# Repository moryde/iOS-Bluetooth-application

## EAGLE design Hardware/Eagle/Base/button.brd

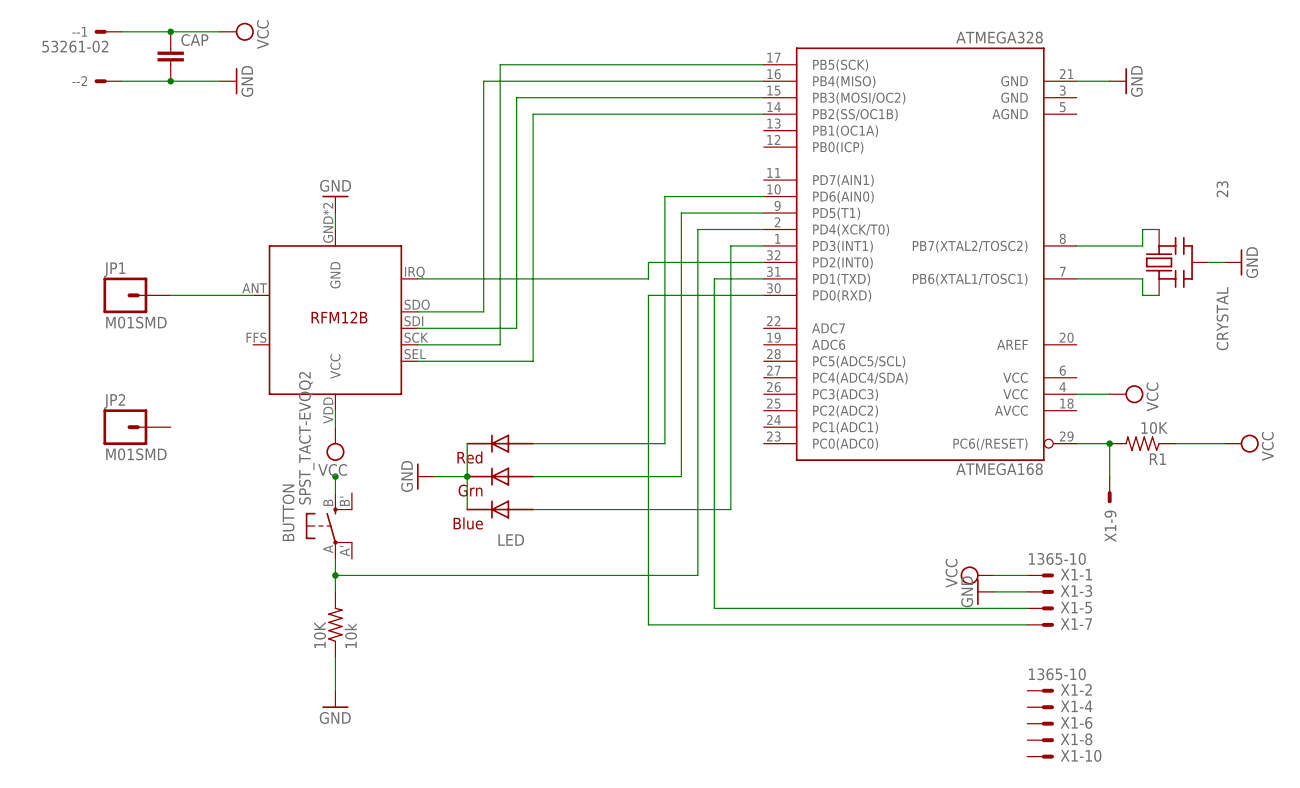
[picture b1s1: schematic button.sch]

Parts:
10K: 10k; R1206
-: 53261-02
ATMEGA328: ATMEGA168; TQFP32-08
BUTTON: SPST_TACT-EVQQ2; EVQ-Q2
CAP: CAP1206; 1206
CRYSTAL: 23; CSTCR-G
JP1, JP2: M01SMD; LUXEON-PAD
LED: RGBLED5050
R1: 10K; R1206
RFM12B: RFM12B
X1: 1365-10

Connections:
5V: -.1, ATMEGA328.4 (VCC), BUTTON.B (S), CAP.1, R1.1, RFM12B.VDD (VCC), X1.1
BUTTON_PIN: 10K.2, ATMEGA328.2 (PD4(XCK/T0)), BUTTON.A
GND: 10K.1, -.2, ATMEGA328.21 (GND), CAP.2, CRYSTAL.2 (GND), LED.4 (BLUE_C), LED.5 (RED_C), LED.6 (GREEN_C), RFM12B.GND, RFM12B.P$12 (GND), X1.3
unnamed: ATMEGA328.8 (PB7(XTAL2/TOSC2)), CRYSTAL.3 (OUT)
unnamed: ATMEGA328.17 (PB5(SCK)), RFM12B.SCK
unnamed: ATMEGA328.15 (PB3(MOSI/OC2)), RFM12B.SDI
unnamed: ATMEGA328.14 (PB2(SS/OC1B)), RFM12B.SEL
unnamed: ATMEGA328.16 (PB4(MISO)), RFM12B.SDO
unnamed: ATMEGA328.7 (PB6(XTAL1/TOSC1)), CRYSTAL.1 (IN)
unnamed: ATMEGA328.1 (PD3(INT1)), LED.3 (BLUE_A)
unnamed: ATMEGA328.32 (PD2(INT0)), RFM12B.IRQ
unnamed: JP1.P$1, RFM12B.ANT
unnamed: ATMEGA328.10 (PD6(AIN0)), LED.2 (RED_A)
unnamed: ATMEGA328.9 (PD5(T1)), LED.1 (GREEN_A)
unnamed: ATMEGA328.31 (PD1(TXD)), X1.5
unnamed: ATMEGA328.30 (PD0(RXD)), X1.7
NANE: ATMEGA328.29 (PC6(/RESET)), R1.2, X1.9

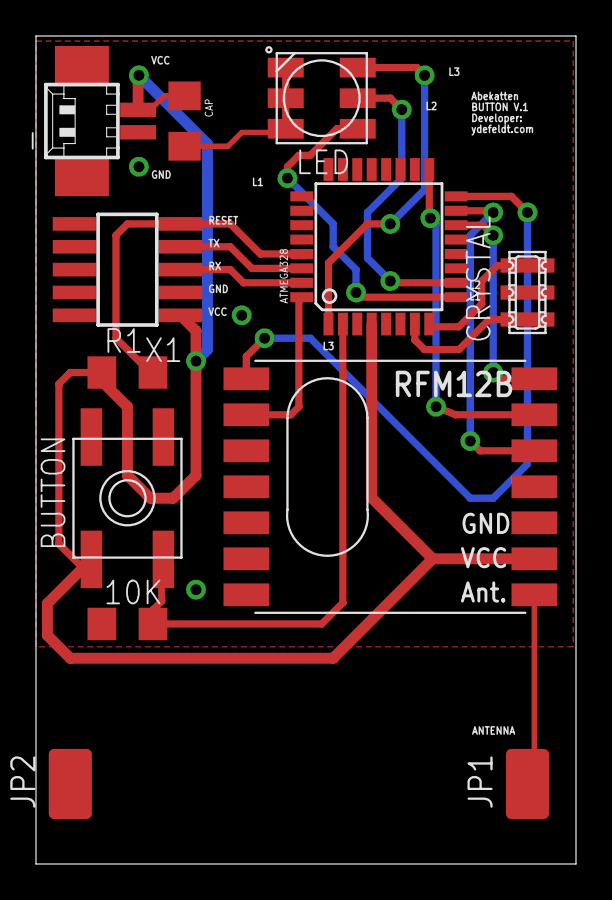
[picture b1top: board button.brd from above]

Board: 2 copper layers, 30.0 x 46.0 mm, 12 parts (0 on the bottom side), 17 nets.

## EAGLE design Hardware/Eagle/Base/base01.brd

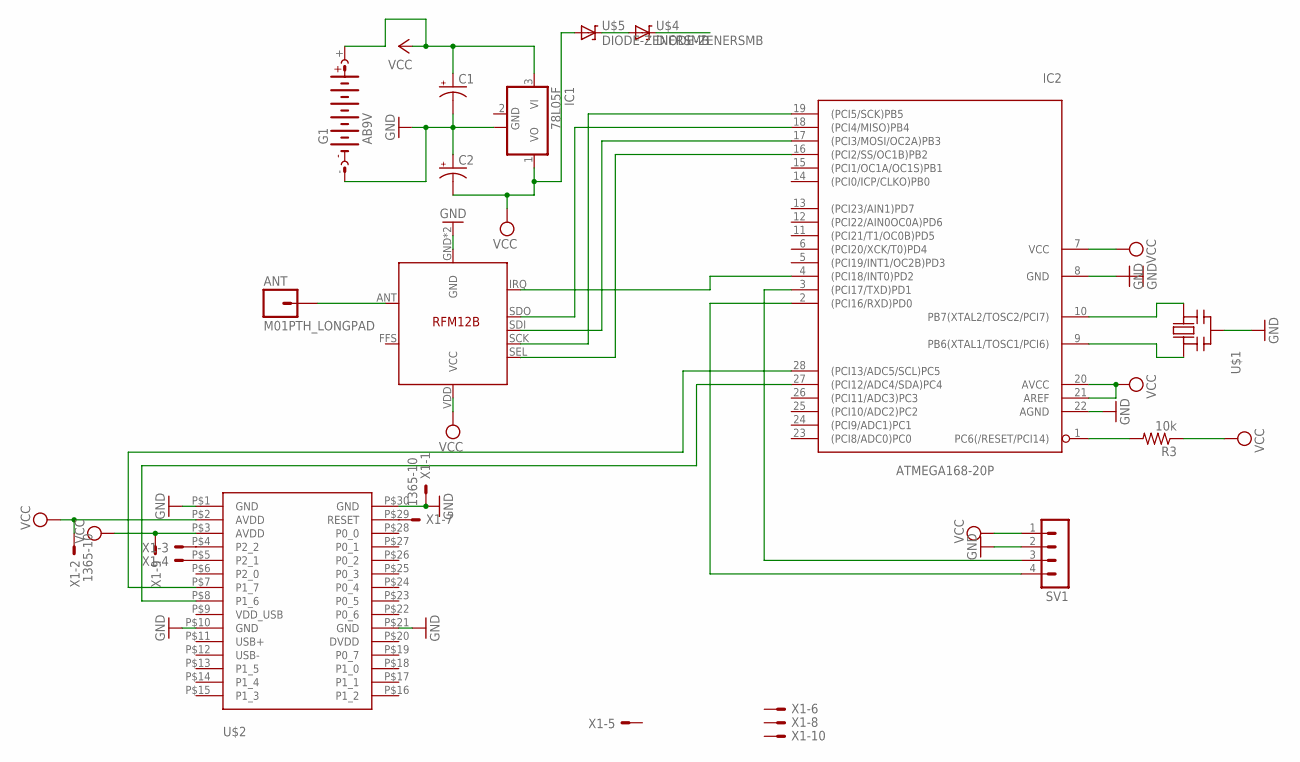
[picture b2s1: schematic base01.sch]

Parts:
ANT: M01PTH_LONGPAD; 1X01_LONGPAD
C1, C2: CAP_POLC; PANASONIC_C
G1: AB9V
IC1: 78L05F; SOT89
IC2: ATMEGA168-20P; DIL28-3
R3: 10k; R2512
SV1: MA04-1
U$1: CERMOSCILL-CSTCRG; CSTCR-G
U$2: BLE112
U$3: RFM12BRMF12BGND; RFM12B
U$4, U$5: DIODE-ZENERSMB; SMB-DIODE
X1: 1365-10

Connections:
GND: C1.-, C2.+, G1.-, IC1.2@1 (GND), IC2.8 (GND), IC2.22 (AGND), SV1.2, U$1.2 (GND), U$2.P$1 (GND), U$2.P$10 (GND), U$2.P$21 (GND), U$2.P$30 (GND), U$3.GND, U$3.P$12 (GND), X1.1
unnamed: IC2.28 ((PCI13/ADC5/SCL)PC5), U$2.P$7 (P1_7)
unnamed: IC2.9 (PB6(XTAL1/TOSC1/PCI6)), U$1.1 (IN)
unnamed: IC2.4 ((PCI18/INT0)PD2), U$3.IRQ
unnamed: IC2.16 ((PCI2/SS/OC1B)PB2), U$3.SEL
unnamed: IC2.19 ((PCI5/SCK)PB5), U$3.SCK
unnamed: IC2.17 ((PCI3/MOSI/OC2A)PB3), U$3.SDI
unnamed: IC2.3 ((PCI17/TXD)PD1), SV1.3
unnamed: IC2.27 ((PCI12/ADC4/SDA)PC4), U$2.P$8 (P1_6)
unnamed: U$2.P$29 (RESET), X1.7
unnamed: IC2.2 ((PCI16/RXD)PD0), SV1.4
unnamed: U$2.P$4 (P2_2), X1.3
unnamed: U$2.P$5 (P2_1), X1.4
unnamed: IC2.10 (PB7(XTAL2/TOSC2/PCI7)), U$1.3 (OUT)
unnamed: IC2.18 ((PCI4/MISO)PB4), U$3.SDO
unnamed: U$4.A, U$5.C
unnamed: ANT.1, U$3.ANT
unnamed: IC2.1 (PC6(/RESET/PCI14)), R3.2
VCC: U$2.P$3 (AVDD), X1.9
VCC3V: U$2.P$2 (AVDD), U$4.C, X1.2
VCC5V: C2.-, IC1.1 (VO), IC2.7 (VCC), IC2.20 (AVCC), IC2.21 (AREF), R3.1, SV1.1, U$3.VDD (VCC), U$5.A
VCCBAT: C1.+, G1.+, IC1.3 (VI)

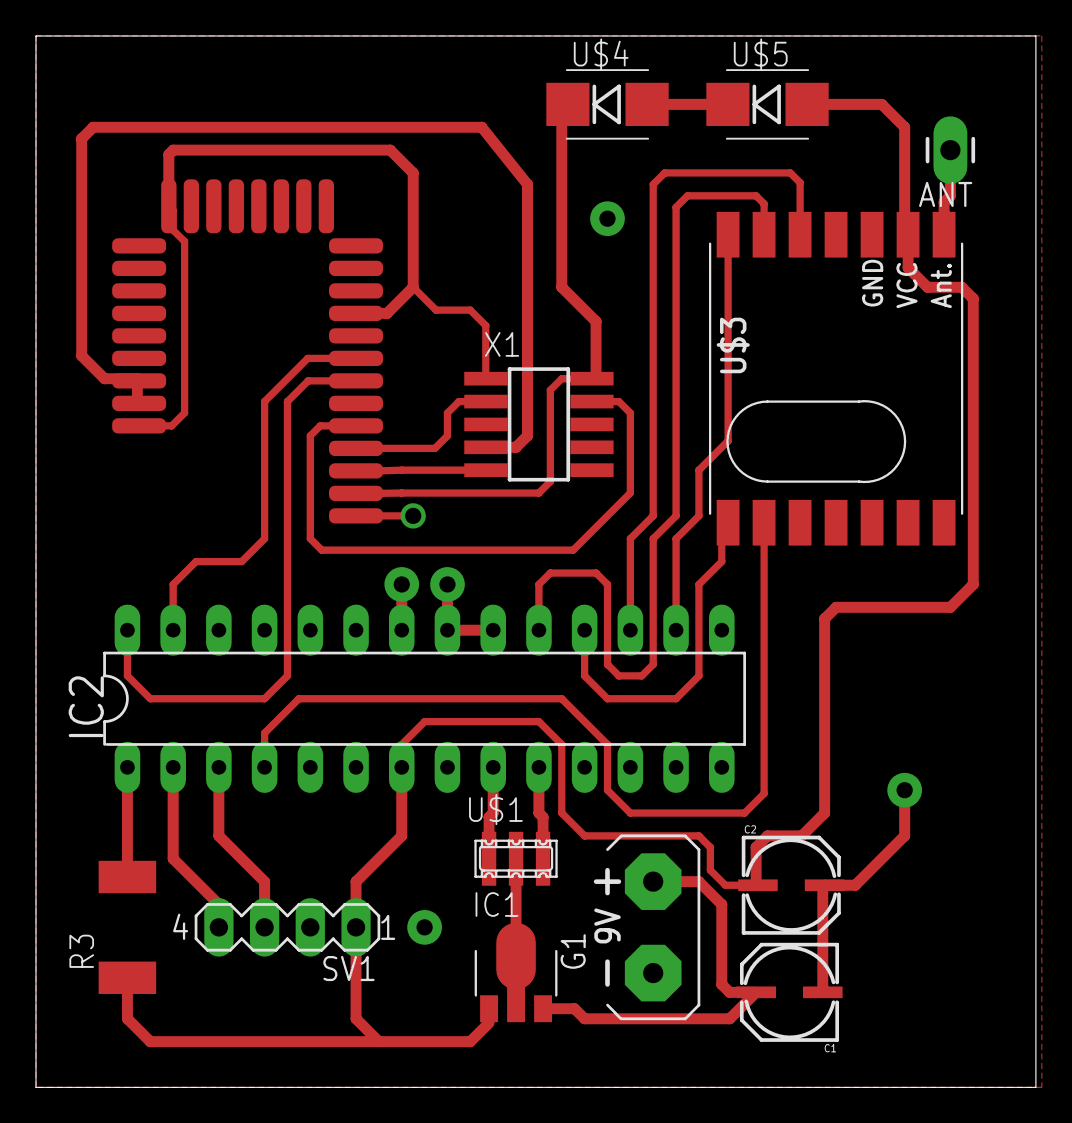
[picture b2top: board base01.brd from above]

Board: 2 copper layers, 55.5 x 58.4 mm, 14 parts (0 on the bottom side), 22 nets.

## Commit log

2013-11-28 Init
2013-11-28 test
2013-11-29 Added smarter button methods
2013-11-29 Further development. Implemented: select buttons to use for games, and time attack game working for multiple button object. [Not tested]
2013-12-09 Added: Domination game, Vibration on press of button.
2013-12-12 HW added
2013-12-13 [HW] Fixed pins for RGB LED
2013-12-13 [HW] Added ping command
2013-12-14 Fixed game Domination so that it will not turn the same LED on again and points are only given if the correct button is pressed.
2013-12-28 Word in progress
2013-12-30 Implementation
2013-12-30 Choose vibration, variable background
2014-01-01 Added gitignore
2014-01-01 added ingore
2014-01-01 Add hardware files
2014-01-01 Added all files for the project
2014-01-01 Added Arduino libraries
2014-01-02 Bug with button pressed delegate not added
2014-01-03 Hardware changes
2014-01-03 Button hardware changes
2014-01-03 Added Cocoa pods support
2014-01-03 Added CorePlot library
    CorePlot is not used for anything useful at this point
2014-01-04 Implementing UICollectionView in selectButtonViewController
2014-01-07 Brought to working state.
2014-01-13 added collectionView

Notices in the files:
parts and their libraries:
SparkFun: Licensing: CC v3.0 Share-Alike You are welcome to use this library for commercial purposes.
